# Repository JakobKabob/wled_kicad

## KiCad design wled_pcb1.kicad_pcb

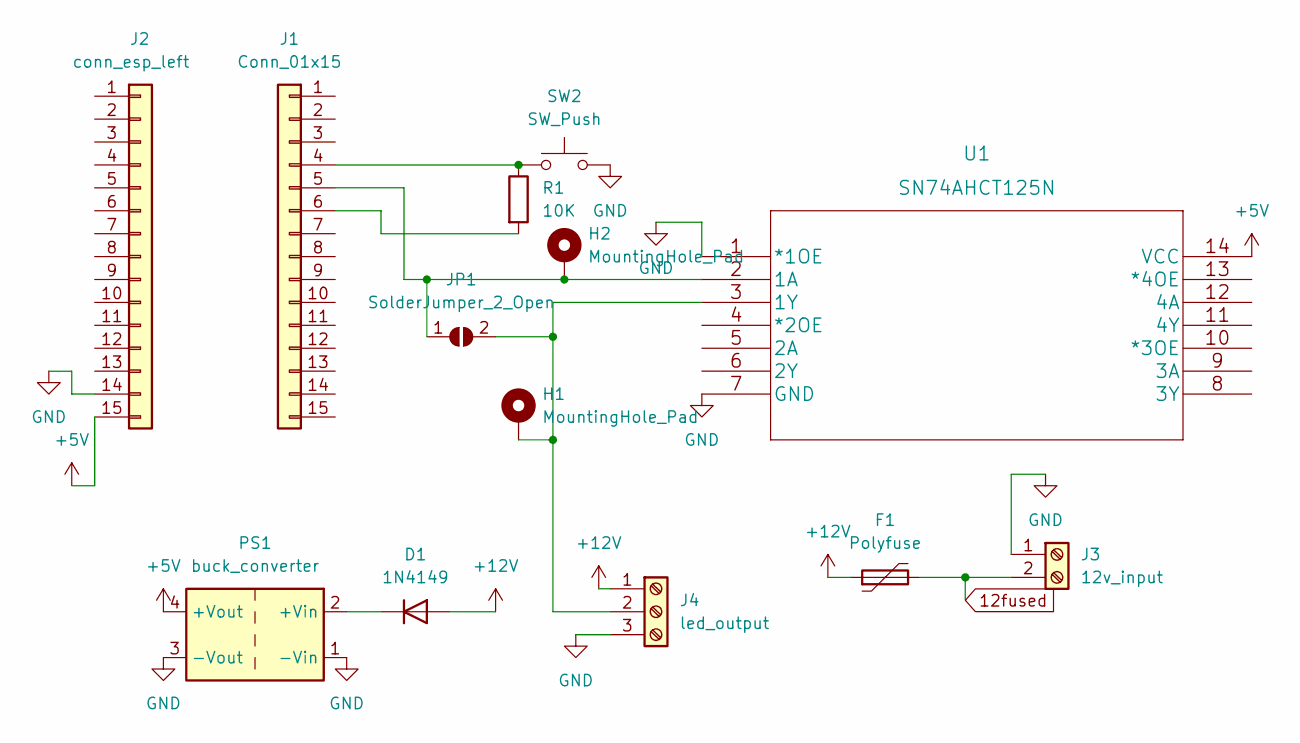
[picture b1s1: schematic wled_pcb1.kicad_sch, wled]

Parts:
D1: 1N4149; D_DO-35_SOD27_P7.62mm_Horizontal
F1: Polyfuse; Fuse_Bourns_MF-RHT500
H1, H2: MountingHole_Pad; Pin_D1.0mm_L10.0mm
J1: Conn_01x15; PinSocket_1x15_P2.54mm_Vertical
J2: conn_esp_left; PinSocket_1x15_P2.54mm_Vertical
J3: 12v_input; TerminalBlock_bornier-2_P5.08mm
J4: led_output; TerminalBlock_bornier-3_P5.08mm
JP1: SolderJumper_2_Open; SolderJumper-2_P1.3mm_Open_RoundedPad1.0x1.5mm
PS1: buck_converter; mini560_AR7
R1: 10K; R_Axial_DIN0207_L6.3mm_D2.5mm_P10.16mm_Horizontal
SW2: SW_Push; button_pianoswitch
U1: SN74AHCT125N

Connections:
12fused: F1.2, J3.2
+5V: J2.15, PS1.4 (+Vout), U1.14 (VCC)
+12V: D1.2 (A), F1.1, J4.1
GND: J2.14, J3.1, J4.3, PS1.1 (-Vin), PS1.3 (-Vout), SW2.2, U1.1 (*1OE), U1.7 (GND)
unnamed: D1.1 (K), PS1.2 (+Vin)
unnamed: H1.1, J4.2, JP1.2 (B), U1.3 (1Y)
unnamed: H2.1, J1.5, JP1.1 (A), U1.2 (1A)
unnamed: J1.4, R1.1, SW2.1
unnamed: J1.6, R1.2

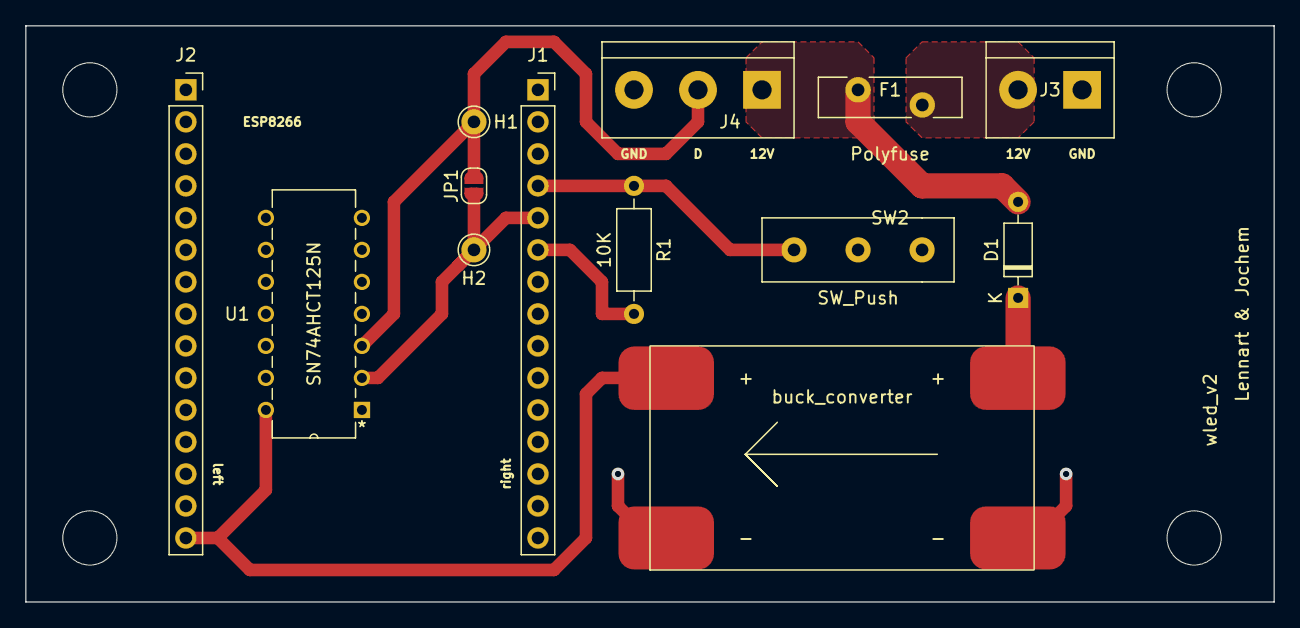
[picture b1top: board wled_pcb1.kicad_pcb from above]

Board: 2 copper layers, 99.1 x 45.7 mm, 13 parts (0 on the bottom side), 9 nets.

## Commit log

2022-02-16 aergthth
2022-02-17 cleanup and update
2022-02-17 printable?
2022-02-17 switched switch outline layer

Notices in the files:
parts and their libraries:
Copyright 2021 Accelerated Designs. All rights reserved.
